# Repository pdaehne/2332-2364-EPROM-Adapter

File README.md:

# 2332/2364 to EPROM Adapter

This repository contains the KiCad project and Gerber files for an adapter that
allows to replace 2332 and 2364 ROMs with 2764, 27128, 27256 or 27512 EPROMs.

> [!WARNING]
> This adapter is currently only used for replacing 2364 ROMs. Replacing 2332
> ROMs is untested! Use at your own risk!

## Ordering the PCB

The subdirectory "gerber-files" contains a Zip file you can use to order the PCB
from PCB manufacturers like PCBWay or JLCPCB. Simply upload the Zip on their web
page. I recommend to use the standard PCB thickness of 1.6mm and HASL finishing.

## Building the Adapter

### Bill of Materials

* __2x 1x12 Pin Straight Male Precision Header 2.54mm pitch__.

  Used to connect the adapter with the socket of the ROM. Make sure that you use
  precision headers (round/machined pins) and not standard square pin headers,
  because these will wear off the socket!

* __1x DIP28 Precision Socket 2.54mm pitch 15.24mm width__.

  Used to connect the EPROM to the adapter. I recommend to use a precision
  socket, because standard sockets with double spring contacts collide with the
  pin headers. When you use standard sockets, you have to cut the pin headers.

* __3x (when replacing a 2364) or 4x (when replacing a 2332) 10kOhm SMD Resistors 0805 size__.

  These are pull-up resistors for the address lines A13 (R2), A14 (R3) and A15
  (R4). When replacing a 2332, you need another pull-up resistor on address line
  A12 (R1).

* __3x (when replacing a 2364) or 4x (when replacing a 2332) 1x2 Pin Header 2.54mm pitch__.

  These are used to externally switch the address lines A13, A14, and A15. When
  replacing a 2332, you need another pin header for address line A12. You may
  use straight or angled pin headers, depending on the space available around
  the adapter. When using straight pins, you need space above the adapter, and
  when using angled, you need space to the side of the adapter.

* __3x (when replacing a 2364) or 4x (when replacing a 2332) Jumper 2.54mm pitch__.

  These are used to externally switch the address lines A13, A14, and A15. When
  replacing a 2332, you need another Jumper for address line A12. These jumpers
  can also replaced by switches or a microcontroller, this depends on how you
  want to switch the contents of the EPROM.

### Soldering the Pull-Up Resistors R1, R2, R3 and R4

You have to start with soldering the resistors on the top of the PCB, because
they are located under the socket. These are the only SMD parts and quite fiddly
to solder by hand. When replacing a __2332__ ROM, you have to populate all four
resistors R1, R2, R3 and R4. When replacing a __2364__ ROM, you only have to
populate the three resistors R2, R3 and R4, __R1 must not be populated__!

### Prepare the Jumper JP1

When replacing a __2332__ ROM, you have to cut the jumper JP1 on the bottom of
the PCB. Be careful and use a sharp cutter knife, and check with a multimeter
that there is no continuity! When replacing a __2364__ ROM, you have to leave
JP1 connected as it is.

### Soldering the Pin Headers

Now, solder the two 12 pins precision pin headers to the PCB. As I said above,
please use precision (round/machined) pin headers instead of the standard square
pin headers, even though they are quite expensive, otherwise you will wear off
the socket. The round pin headers will also wear off the socket, but much less
than the standard pin headers.

Be careful to use the correct location on the bottom side of the PCB - use the
two shorter rows of 12 holes marked with rectangles on the silk screen!

It is crucial that you solder these pins straight to the PCB, otherwise they
will not fit into the socket later. I used an old breadboard as a soldering aid,
but it sucks away a lot of heat, and you will need to apply a lot of heat when
soldering. Be careful not to drop any solder onto the breadboard!

### Soldering the Socket

Solder the socket to the top of the PCB. Mind the orientation, the notch of the
socket should face in the direction marked on the silk screen (to the right in
the image below). When you do __not__ use a precision socket (which I
recommend), you have to cut the pins soldered in the previous step with a side
cutter so that the socket sits flush on the PCB.

Soldering is quite fiddly, because you have to solder next to and in between the
pin headers. Be careful not to melt the plastic of the pin headers!

### Soldering the Pin Headers for the Address Lines

The last step is to solder the pin headers for the address lines. When replacing
a 2332 ROM, solder the pin headers for address lines A12, A13, A14 and A15. When
replacing a 2364 ROM, solder the pin headers only for address lines A13, A14 and
A15. Do not solder a pin header for A12!

Make sure to solder the pin headers as straight as possible. In the images
below, I use an adhesive like
[Blu Tack](https://en.wikipedia.org/wiki/Blu_Tack).

## Using the Adapter

Carefully push the adapter into the ROM socket. Mind the orientation - the notch
of the ROM socket and the notch of the EPROM socket on the adapter must point to
the same direction! Try not to repeatedly insert and remove the adapter - it
wears off the ROM socket!

## License

2332/2364 to EPROM Adapter (c) by Patrick Dähne

2332/2364 to EPROM Adapter is licensed under a
Creative Commons Attribution-NonCommercial-ShareAlike 4.0 International License.

You should have received a copy of the license along with this
work. If not, see <https://creativecommons.org/licenses/by-nc-sa/4.0/>.

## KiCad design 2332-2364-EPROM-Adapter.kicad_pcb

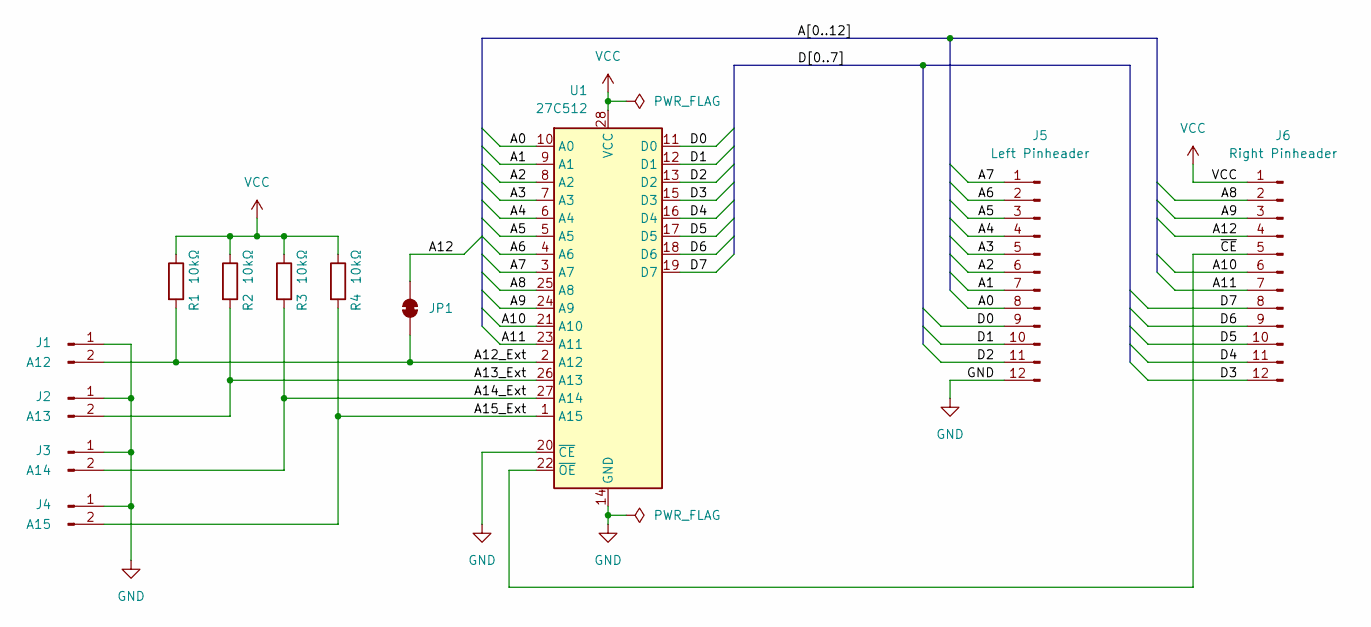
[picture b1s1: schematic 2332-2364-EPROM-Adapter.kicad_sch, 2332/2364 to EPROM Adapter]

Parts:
J1: A12; PinHeader_1x02_P2.54mm_Vertical
J2: A13; PinHeader_1x02_P2.54mm_Vertical
J3: A14; PinHeader_1x02_P2.54mm_Vertical
J4: A15; PinHeader_1x02_P2.54mm_Vertical
J5: Left Pinheader; PinHeader_1x12_P2.54mm_Vertical
J6: Right Pinheader; PinHeader_1x12_P2.54mm_Vertical
JP1: SolderJumper-2_P1.3mm_Bridged_RoundedPad1.0x1.5mm
R1, R2, R3, R4: 10kΩ; R_0805_2012Metric_Pad1.20x1.40mm_HandSolder
U1: 27C512; DIP-28_W15.24mm_Socket

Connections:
/A0: J5.8, U1.10 (A0)
/A1: J5.7, U1.9 (A1)
/A2: J5.6, U1.8 (A2)
/A3: J5.5, U1.7 (A3)
/A4: J5.4, U1.6 (A4)
/A5: J5.3, U1.5 (A5)
/A6: J5.2, U1.4 (A6)
/A7: J5.1, U1.3 (A7)
/A8: J6.2, U1.25 (A8)
/A9: J6.3, U1.24 (A9)
/A10: J6.6, U1.21 (A10)
/A11: J6.7, U1.23 (A11)
/A12: J6.4, JP1.2 (B)
/A12_Ext: J1.2, JP1.1 (A), R1.2, U1.2 (A12)
/A13_Ext: J2.2, R2.2, U1.26 (A13)
/A14_Ext: J3.2, R3.2, U1.27 (A14)
/A15_Ext: J4.2, R4.2, U1.1 (A15)
/D0: J5.9, U1.11 (D0)
/D1: J5.10, U1.12 (D1)
/D2: J5.11, U1.13 (D2)
/D3: J6.12, U1.15 (D3)
/D4: J6.11, U1.16 (D4)
/D5: J6.10, U1.17 (D5)
/D6: J6.9, U1.18 (D6)
/D7: J6.8, U1.19 (D7)
/~CE: J6.5, U1.22 (~OE)
GND: J1.1, J2.1, J3.1, J4.1, J5.12, U1.14 (GND), U1.20 (~CE)
VCC: J6.1, R1.1, R2.1, R3.1, R4.1, U1.28 (VCC)

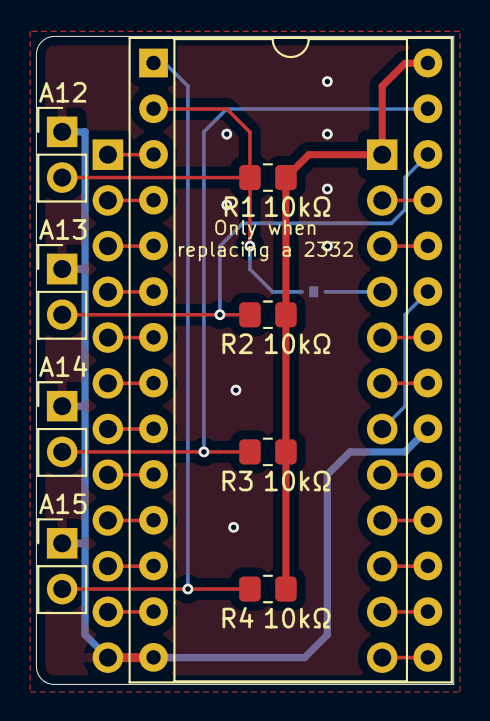
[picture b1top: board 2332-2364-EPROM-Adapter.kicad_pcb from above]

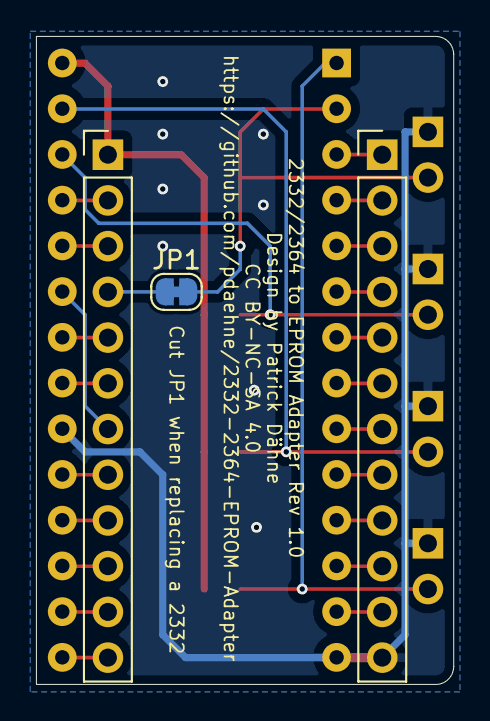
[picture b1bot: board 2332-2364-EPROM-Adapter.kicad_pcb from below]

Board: 2 copper layers, 23.2 x 36.0 mm, 12 parts (3 on the bottom side), 28 nets.

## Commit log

2025-01-20 Initial check-in
2025-01-20 Added pictures for cutting JP1
2025-01-20 Added missing pictures

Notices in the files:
2332-2364-EPROM-Adapter.kicad_pcb:
Patrick Dähne CC BY-NC-SA 4.0
CC BY-NC-SA 4.0
